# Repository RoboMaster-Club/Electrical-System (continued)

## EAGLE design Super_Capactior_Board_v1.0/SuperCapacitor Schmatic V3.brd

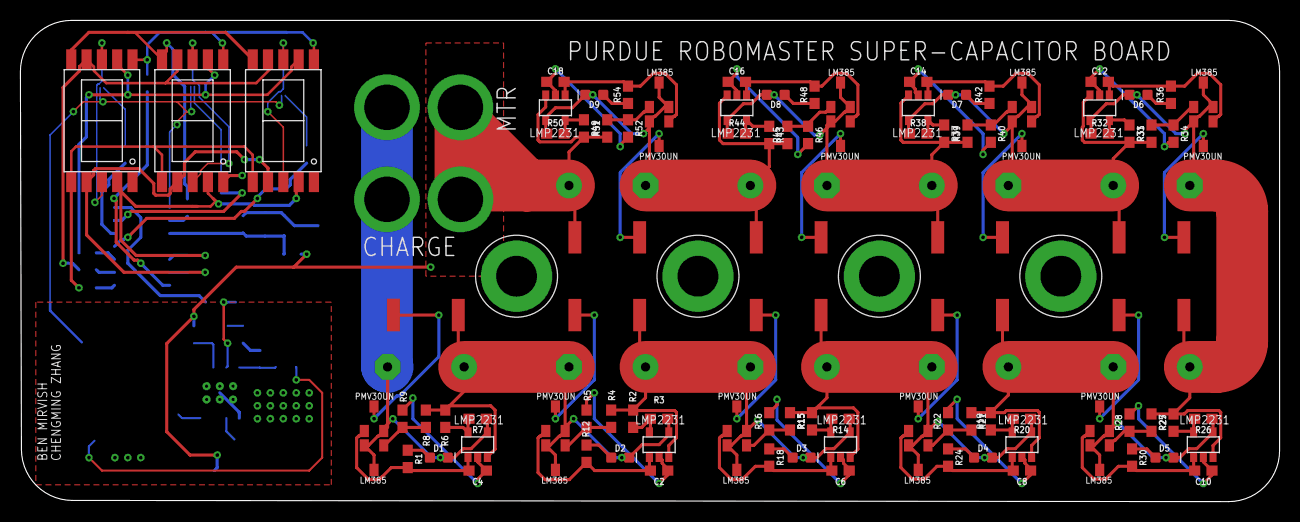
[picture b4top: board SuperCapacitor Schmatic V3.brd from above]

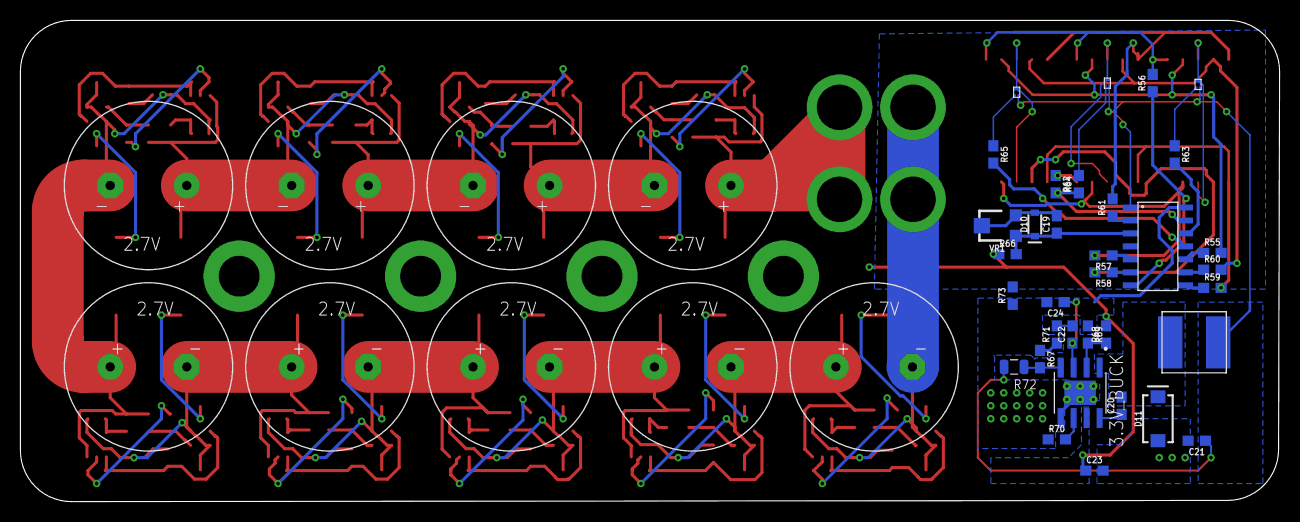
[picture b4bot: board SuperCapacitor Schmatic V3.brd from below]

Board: 2 copper layers, 123.4 x 47.2 mm, 151 parts (43 on the bottom side), 98 nets.

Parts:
3.3V_BUCK: SOIC8E; SOIC127P600X170-9N
C1, C3, C5, C7, C9, C11, C13, C15, C17: 2.7V 60F; 2.7V_60F
C2, C4, C6, C8, C10, C12, C14, C16, C18: 100pF; 0603
C19, C20, C21, C22, C23: 0.1uF; 0603
C24: 0.22uF; 0603
CHARGE: XT60_CIRCLE
D1, D2, D3, D4, D5, D6, D7, D8, D9: RED; LED-0603
D10: 5.1V; SOD-323
D11: 3A/40V/500mV; SMA-DIODE
MTR: XT60_CIRCLE
R1, R12, R18, R24, R30, R36, R42, R48, R54, R63, R64, R65, R67: 1k; 0603
R2, R6, R13, R19, R25, R31, R37, R43, R49: 75k; 0603@1
R3, R7, R14, R20, R26, R32, R38, R44, R50: 61.9k; 0603@1
R4, R8, R15, R21, R27, R33, R39, R45, R51: 33K,1%; 0603@1
R5, R9, R16, R22, R28, R34, R40, R46, R52, R68, R69, R70, R71: 10k; 0603
R10, R11, R17, R23, R29, R35, R41, R47, R53: 0.05; 2512
R55, R56, R57, R58, R59, R60, R61, R62: 100; 0603
R66: 47k; 0603
R72: 5.25k; RES_0805
R73: 0; 0603
U$1, U$4, U$7, U$10, U$13, U$16, U$19, U$22, U$25: LMP2231; LMP2231_SOT23_5
U$2, U$5, U$8, U$11, U$14, U$17, U$20, U$23, U$26: LM385; LM385_SOT23
U$3, U$6, U$9, U$12, U$15, U$18, U$21, U$24, U$27: PMV30UN_MOS; PMV30UN_SOT23
U$30, U$31, U$32, U$33: M5
U$35, U$36, U$37: DSM7T; 7-SEGMENT_SMD
U$38: PIC16F676
U$39: 4.7UH_INDUCTOR
U$40, U$41, U$42: SOT_223; BC856BMB
VR1: 10k; TRIMPOT-SMD-TC33X

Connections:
1: R17.P$1, U$9.DRAIN
5V_PWR: C21.1, R72.2, U$38.1, U$39.P$2, U$40.P$2, U$41.P$2, U$42.P$2
ALT_GND: 3.3V_BUCK.5, 3.3V_BUCK.9, C21.2, C23.2, C24.2, D11.A, R67.1, R69.1, R70.1, R71.1, R73.1, U$38.14
A_CNTL: R55.1, U$38.10
BUCK_ENABLE: 3.3V_BUCK.2, R68.1, R69.2
B_CNTL: R56.1, U$38.7
C_CNTL: R57.1, U$38.5
D_CNTL: R58.1, U$38.6
E_CNTL: R59.1, U$38.8
F_CNTL: R60.1, U$38.9
GND: C3.-, C19.2, CHARGE.2, D1.C, D10.A, MTR.2, R7.1, R73.2, U$4.IN-, U$5.-, U$5.FB, U$6.SOURCE, VR1.2, VR1.3
G_CNTL: R61.1, U$38.2
unnamed: D1.A, R1.1
unnamed: U$37.3, U$37.8, U$41.P$1
unnamed: C2.2, R12.2, U$1.OUT, U$3.GATE
unnamed: C1.-, C3.+, D2.C, R3.1, R6.2, R8.1, R10.P$2, U$1.IN-, U$2.-, U$2.FB, U$3.SOURCE, U$4.IN+
unnamed: R2.1, R3.2, U$1.V+
unnamed: C2.1, R5.2, U$1.V-
unnamed: R4.2, R5.1, U$2.+
unnamed: U$36.3, U$36.8, U$42.P$1
unnamed: C4.2, R1.2, U$4.OUT, U$6.GATE
unnamed: R63.1, U$40.P$3
unnamed: R6.1, R7.2, U$4.V+
unnamed: C4.1, R9.2, U$4.V-
unnamed: R8.2, R9.1, U$5.+
unnamed: R10.P$1, U$6.DRAIN
unnamed: R11.P$1, U$3.DRAIN
unnamed: D2.A, R12.1
unnamed: R64.2, U$41.P$3
unnamed: C6.2, R18.2, U$7.OUT, U$9.GATE
unnamed: C1.+, C5.-, D3.C, R2.2, R4.1, R11.P$2, R14.1, U$1.IN+, U$7.IN-, U$8.-, U$8.FB, U$9.SOURCE
unnamed: R13.1, R14.2, U$7.V+
unnamed: C6.1, R16.2, U$7.V-
unnamed: R15.2, R16.1, U$8.+
unnamed: R62.1, U$37.5
unnamed: D3.A, R18.1
unnamed: R62.2, R64.1, U$38.13
unnamed: C8.2, R24.2, U$10.OUT, U$12.GATE
unnamed: C5.+, C7.-, D4.C, R13.2, R15.1, R17.P$2, R20.1, U$7.IN+, U$10.IN-, U$11.-, U$11.FB, U$12.SOURCE
unnamed: R19.1, R20.2, U$10.V+
unnamed: C8.1, R22.2, U$10.V-
unnamed: R21.2, R22.1, U$11.+
unnamed: R23.P$1, U$12.DRAIN
unnamed: D4.A, R24.1
unnamed: R63.2, U$38.12
unnamed: C10.2, R30.2, U$13.OUT, U$15.GATE
unnamed: C7.+, C9.-, D5.C, R19.2, R21.1, R23.P$2, R26.1, U$10.IN+, U$13.IN-, U$14.-, U$14.FB, U$15.SOURCE
unnamed: R25.1, R26.2, U$13.V+
unnamed: C10.1, R28.2, U$13.V-
unnamed: R27.2, R28.1, U$14.+
unnamed: R29.P$1, U$15.DRAIN
unnamed: D5.A, R30.1
unnamed: C19.1, D10.C, R66.2, U$38.3, VR1.1
unnamed: C12.2, R36.2, U$16.OUT, U$18.GATE
unnamed: C9.+, C11.-, D6.C, R25.2, R27.1, R29.P$2, R32.1, U$13.IN+, U$16.IN-, U$17.-, U$17.FB, U$18.SOURCE
unnamed: R31.1, R32.2, U$16.V+
unnamed: C12.1, R34.2, U$16.V-
unnamed: R33.2, R34.1, U$17.+
unnamed: R35.P$1, U$18.DRAIN
unnamed: D6.A, R36.1
unnamed: R65.2, U$38.11
unnamed: C14.2, R42.2, U$19.OUT, U$21.GATE
unnamed: C11.+, C13.-, D7.C, R31.2, R33.1, R35.P$2, R38.1, U$16.IN+, U$19.IN-, U$20.-, U$20.FB, U$21.SOURCE
unnamed: R37.1, R38.2, U$19.V+
unnamed: C14.1, R40.2, U$19.V-
unnamed: R39.2, R40.1, U$20.+
unnamed: R41.P$1, U$21.DRAIN
unnamed: D7.A, R42.1
unnamed: U$35.3, U$35.8, U$40.P$1
unnamed: C16.2, R48.2, U$22.OUT, U$24.GATE
unnamed: C13.+, C15.-, D8.C, R37.2, R39.1, R41.P$2, R44.1, U$19.IN+, U$22.IN-, U$23.-, U$23.FB, U$24.SOURCE
unnamed: R43.1, R44.2, U$22.V+
unnamed: C16.1, R46.2, U$22.V-
unnamed: R45.2, R46.1, U$23.+
unnamed: R47.P$1, U$24.DRAIN
unnamed: D8.A, R48.1
unnamed: R65.1, U$42.P$3
unnamed: C18.2, R54.2, U$25.OUT, U$27.GATE
unnamed: C15.+, C17.-, D9.C, R43.2, R45.1, R47.P$2, R50.1, U$22.IN+, U$25.IN-, U$26.-, U$26.FB, U$27.SOURCE
unnamed: R49.1, R50.2, U$25.V+
unnamed: C18.1, R52.2, U$25.V-
unnamed: R51.2, R52.1, U$26.+
unnamed: R53.P$1, U$27.DRAIN
unnamed: D9.A, R54.1
unnamed: R55.2, U$35.7, U$36.7, U$37.7
unnamed: R56.2, U$35.6, U$36.6, U$37.6
unnamed: R57.2, U$35.4, U$36.4, U$37.4
unnamed: R58.2, U$35.2, U$36.2, U$37.2
unnamed: R59.2, U$35.1, U$36.1, U$37.1
unnamed: R60.2, U$35.9, U$36.9, U$37.9
unnamed: R61.2, U$35.10, U$36.10, U$37.10
unnamed: 3.3V_BUCK.4, R67.2, R72.1
unnamed: 3.3V_BUCK.8, C20.1
unnamed: 3.3V_BUCK.6, R70.2
unnamed: 3.3V_BUCK.3, C22.1, C24.1
unnamed: C22.2, R71.2
SW: 3.3V_BUCK.1, C20.2, D11.C, U$39.P$1
VCC: 3.3V_BUCK.7, C17.+, C23.1, CHARGE.1, MTR.1, R49.2, R51.1, R53.P$2, R66.1, R68.2, U$25.IN+
